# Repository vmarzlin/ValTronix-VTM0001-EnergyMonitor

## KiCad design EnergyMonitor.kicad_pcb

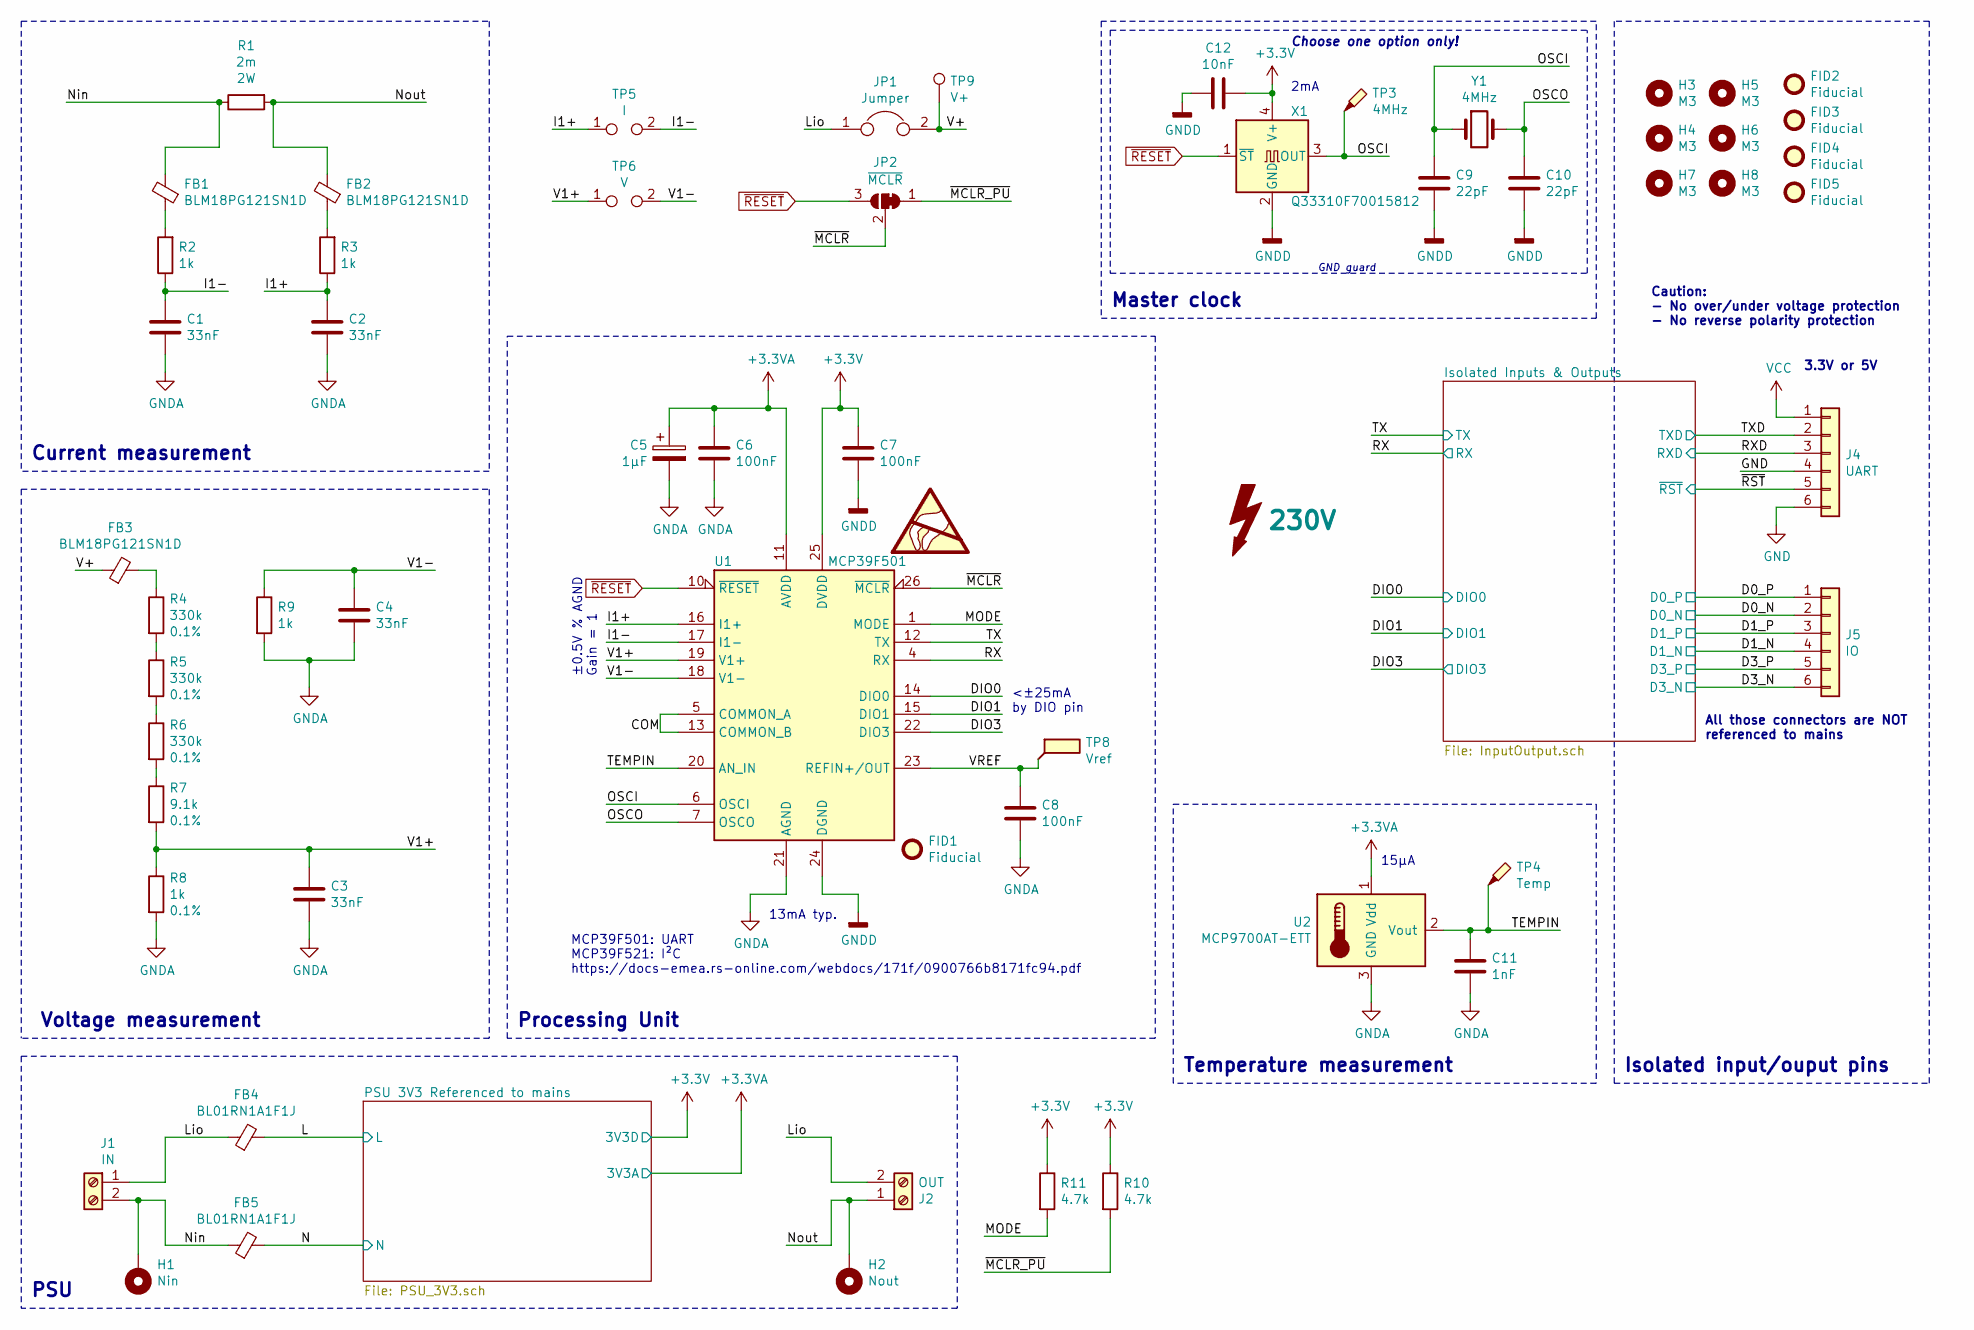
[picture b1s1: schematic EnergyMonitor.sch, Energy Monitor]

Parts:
C1, C2, C3, C4: 33nF; C_0805
C5: 1µF; CP_Elec_4x5.7
C6, C7: 100nF; C_1206
C8: 100nF; C_0805
C9, C10: 22pF; C_0805
C11: 1nF; C_0603
C12: 10nF; C_0603
FB1, FB2, FB3: BLM18PG121SN1D; L_0805
FB4, FB5: BL01RN1A1F1J; L_FB_BL01
FID1: Fiducial; Fiducial_0.5mm_Dia_1mm_Outer
FID2, FID3, FID4, FID5: Fiducial; Fiducial_1mm_Dia_2mm_Outer
H1: Nin; MountingHole_3.2mm_M3_ISO14580_Pad
H2: Nout; MountingHole_3.2mm_M3_ISO14580_Pad
H3, H4, H5, H6, H7, H8: M3; MountingHole_3.2mm_M3_DIN965
J1: IN; TerminalBlock_bornier-2_P5.08mm
J2: OUT; TerminalBlock_bornier-2_P5.08mm
J4: UART; Pin_Header_Straight_1x06_Pitch2.54mm
J5: IO; Pin_Header_Straight_1x06_Pitch2.54mm
JP1: Jumper; Pin_Header_Straight_1x02_Pitch2.54mm
JP2: ~MCLR; JP3_SMD_12closed
R1: 2m; R_2512
R2, R3, R8, R9: 1k; R_0805
R4, R5, R6: 330k; R_MicroMELF_MMU-0102
R7: 9.1k; R_MicroMELF_MMU-0102
R10, R11: 4.7k; R_0805
SYM1: 230V; Symbol_HighVoltage_Silk
SYM2: SYM_ESD_Large; ESD-Logo_8.9x8mm_SilkScreen
TP3: 4MHz; Measurement_Point_Round-SMD-Pad_Small
TP4: Temp; Measurement_Point_Round-SMD-Pad_Small
TP5: I; Test_Point_2Pads
TP6: V; Test_Point_2Pads
TP8: Vref; Measurement_Point_Round-SMD-Pad_Small
TP9: V+; Test_Point_Keystone_5019_Minature
U1: MCP39F501; QFN-28-1EP_5x5mm_Pitch0.5mm
U2: MCP9700AT-ETT; SOT-23
X1: Q33310F70015812; Oscillator_SMD_SeikoEpson_SG8002CE-4pin_3.2x2.5mm
Y1: 4MHz; Crystal_HC49-4H_Vertical

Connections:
+3.3VA: C5.1, C6.1, U1.11 (AVDD), U2.1 (Vdd); also elsewhere on the board
/COM: U1.5 (COMMON_A), U1.13 (COMMON_B)
/D0_N: J5.2; also elsewhere on the board
/D0_P: J5.1; also elsewhere on the board
/D1_N: J5.4; also elsewhere on the board
/D1_P: J5.3; also elsewhere on the board
/D3_N: J5.6; also elsewhere on the board
/D3_P: J5.5; also elsewhere on the board
/DIO0: U1.14 (DIO0); also elsewhere on the board
/DIO1: U1.15 (DIO1); also elsewhere on the board
/DIO3: U1.22 (DIO3); also elsewhere on the board
/I1+: C2.1, R3.1, TP5.1, U1.16 (I1+)
/I1-: C1.1, R2.1, TP5.2, U1.17 (I1-)
/L: FB4.2; also elsewhere on the board
/Lio: FB4.1, J1.1, J2.2, JP1.1
/MODE: R11.2, U1.1 (MODE)
/N: FB5.2; also elsewhere on the board
/Nin: FB1.2, FB5.1, H1.1, J1.2, R1.1
/Nout: FB2.2, H2.1, J2.1, R1.2
/OSCI: C9.1, TP3.1, U1.6 (OSCI), X1.3 (OUT), Y1.1
/OSCO: C10.1, U1.7 (OSCO), Y1.2
/RX: U1.4 (RX); also elsewhere on the board
/RXD: J4.3; also elsewhere on the board
/TEMPIN: C11.1, TP4.1, U1.20 (AN_IN), U2.2 (Vout)
/TX: U1.12 (TX); also elsewhere on the board
/TXD: J4.2; also elsewhere on the board
/V1+: C3.1, R7.2, R8.1, TP6.1, U1.19 (V1+)
/V1-: C4.1, R9.1, TP6.2, U1.18 (V1-)
/V+: FB3.1, JP1.2, TP9.1
/VREF: C8.1, TP8.1, U1.23 (REFIN+/OUT)
/~MCLR: JP2.2 (C), U1.26 (~MCLR)
/~MCLR_PU: JP2.1 (A), R10.2
/~RST: J4.5; also elsewhere on the board
GND: J4.4, J4.6; also elsewhere on the board
GNDA: C1.2, C2.2, C3.2, C4.2, C5.2, C6.2, C8.2, C11.2, R8.2, R9.2, U1.21 (AGND), U2.3 (GND); also elsewhere on the board
GNDD: C7.2, C9.2, C10.2, C12.2, U1.24 (DGND), U1.27 (DGND), U1.29 (DGND), X1.2 (GND); also elsewhere on the board
unnamed: FB1.1, R2.2
unnamed: FB2.1, R3.2
unnamed: FB3.2, R4.1
unnamed: R4.2, R5.1
unnamed: R5.2, R6.1
unnamed: R6.2, R7.1
VCC: J4.1; also elsewhere on the board
~RESET: JP2.3 (B), U1.10 (~RESET), X1.1 (~ST); also elsewhere on the board

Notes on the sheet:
MCP39F501: UART MCP39F521: I²C https://docs-emea.rs-online.com/webdocs/171f/0900766b8171fc94.pdf
13mA typ.
±0.5V % AGND Gain = 1
15µA
2mA
GND guard
3.3V or 5V
<±25mA by DIO pin
Isolated input/ouput pins
Current measurement
Voltage measurement
PSU
Temperature measurement
Processing Unit
Master clock
Caution: - No over/under voltage protection - No reverse polarity protection
All those connectors are NOT referenced to mains
Choose one option only!

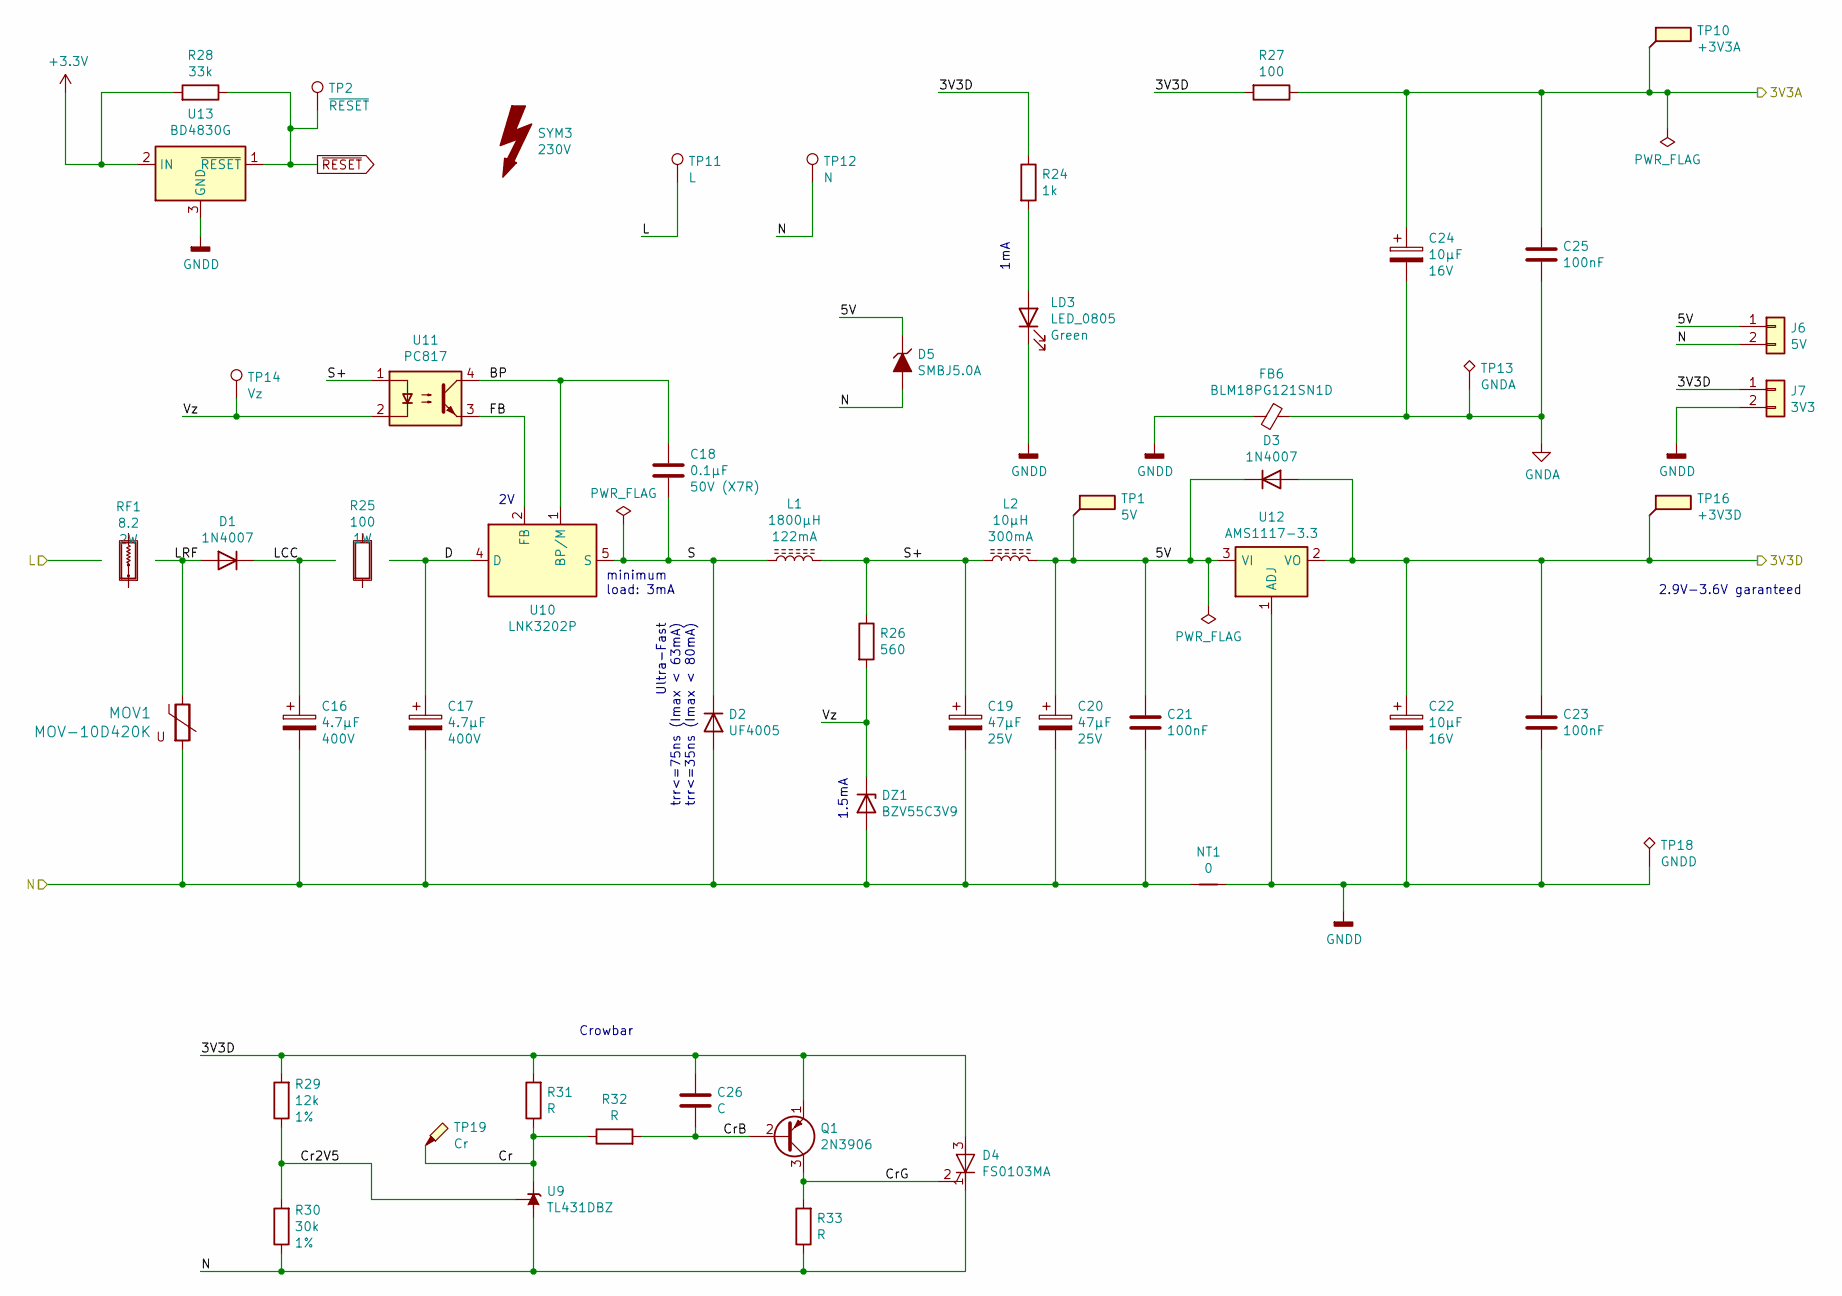
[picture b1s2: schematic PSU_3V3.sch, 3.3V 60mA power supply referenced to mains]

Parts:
C16, C17: 4.7µF; CP_Radial_D10.0mm_P5.00mm; Voltage 400V; Part ULD2G4R7MPD
C18: 0.1µF; C_1206; Voltage 50V (X7R); Part CL31B104KBCNNNL
C19, C20: 47µF; CP_Elec_6.3x7.7; Voltage 25V
C21, C23: 100nF; C_1206
C22, C24: 10µF; CP_Elec_4x5.7; Voltage 16V
C25: 100nF; C_0805
C26: C; C_0805
D1, D3: 1N4007; D_DO-41_SOD81_P10.16mm_Horizontal
D2: UF4005; D_DO-41_SOD81_P10.16mm_Horizontal
D4: FS0103MA; TO-92_Inline_Narrow_Oval
D5: SMBJ5.0A; D_SMB
DZ1: BZV55C3V9; D_MiniMELF
FB6: BLM18PG121SN1D; L_0805
J6: 5V; Pin_Header_Straight_1x02_Pitch2.54mm
J7: 3V3; Pin_Header_Straight_1x02_Pitch2.54mm
L1: 1800µH; L_Bourns_SDR1006; Part SDR1006-182KL
L2: 10µH; L_1210; Part LQH32CN100K23L
LD3: LED_0805
MOV1: MOV-10D420K; RV_Disc_D12_W4.5_P7.5
NT1: 0; R_0805
Q1: 2N3906; TO-92_Inline_Narrow_Oval
R24: 1k; R_0805
R25: 100; R_Axial_DIN0414_L11.9mm_D4.5mm_P15.24mm_Horizontal; Part # ROX2SJ100R
R26: 560; R_0805
R27: 100; R_0805
R28: 33k; R_0805
R29: 12k; R_0805
R30: 30k; R_0805
R31, R32, R33: R; R_0805
RF1: 8.2; R_Axial_DIN0414_L11.9mm_D4.5mm_P15.24mm_Horizontal; Part # PR02000208208JA100
SYM3: 230V; Symbol_HighVoltage_Silk
TP1: 5V; Measurement_Point_Square-SMD-Pad_Big
TP2: ~RESET; Measurement_Point_Round-SMD-Pad_Small
TP10: +3V3A; Measurement_Point_Square-SMD-Pad_Big
TP11: L; Measurement_Point_Square-SMD-Pad_Small
TP12: N; Measurement_Point_Round-TH_Big
TP13: GNDA; Measurement_Point_Round-TH_Big
TP14: Vz; Measurement_Point_Round-SMD-Pad_Small
TP16: +3V3D; Measurement_Point_Square-SMD-Pad_Big
TP18: GNDD; Measurement_Point_Round-TH_Big
TP19: Cr; Measurement_Point_Round-SMD-Pad_Small
U9: TL431DBZ; SOT-23
U10: LNK3202P; PDIP-8C
U11: PC817; DIP-4_W7.62mm_LongPads
U12: AMS1117-3.3; SOT-223-3_TabPin2
U13: BD4830G; SSOP-5_2.9x2.8mm_Pitch0.95mm

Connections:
+3.3VA: C24.1, C25.1, R27.1, TP10.1; also elsewhere on the board
/L: RF1.1, TP11.1; also elsewhere on the board
/N: C16.2, C17.2, C19.2, C20.2, C21.2, D2.2 (A), D4.1 (K), D5.2 (A2), DZ1.2 (A), J6.2, MOV1.2, NT1.2, R30.1, R33.1, TP12.1, U9.3 (A); also elsewhere on the board
/PSU 3V3 Referenced to mains/5V: C20.1, C21.1, D3.1 (K), D5.1 (A1), J6.1, L2.2, TP1.1, U12.3 (VI)
/PSU 3V3 Referenced to mains/BP: C18.1, U10.1 (BP/M), U11.4
/PSU 3V3 Referenced to mains/Cr: R31.1, R32.1, TP19.1, U9.1 (K)
/PSU 3V3 Referenced to mains/Cr2V5: R29.1, R30.2, U9.2 (REF)
/PSU 3V3 Referenced to mains/CrB: C26.2, Q1.2 (B), R32.2
/PSU 3V3 Referenced to mains/CrG: D4.2 (G), Q1.3 (C), R33.2
/PSU 3V3 Referenced to mains/D: C17.1, R25.2, U10.4 (D)
/PSU 3V3 Referenced to mains/FB: U10.2 (FB), U11.3
/PSU 3V3 Referenced to mains/LCC: C16.1, D1.1 (K), R25.1
/PSU 3V3 Referenced to mains/LRF: D1.2 (A), MOV1.1, RF1.2
/PSU 3V3 Referenced to mains/S: C18.2, D2.1 (K), L1.1, U10.5 (S), U10.6 (S), U10.7 (S), U10.8 (S)
/PSU 3V3 Referenced to mains/S+: C19.1, L1.2, L2.1, R26.1, U11.1
/PSU 3V3 Referenced to mains/Vz: DZ1.1 (K), R26.2, TP14.1, U11.2
GNDA: C24.2, C25.2, FB6.1, TP13.1; also elsewhere on the board
GNDD: C22.2, C23.2, FB6.2, J7.2, LD3.1 (K), NT1.1, TP18.1, U12.1 (ADJ), U13.3 (GND); also elsewhere on the board
unnamed: LD3.2 (A), R24.2
~RESET: R28.1, TP2.1, U13.1 (~RESET); also elsewhere on the board

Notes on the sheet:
Ultra-Fast trr<=75ns (Imax < 63mA) trr<=35ns (Imax < 80mA)
1.5mA
minimum load: 3mA
Crowbar
1mA
2.9V-3.6V garanteed

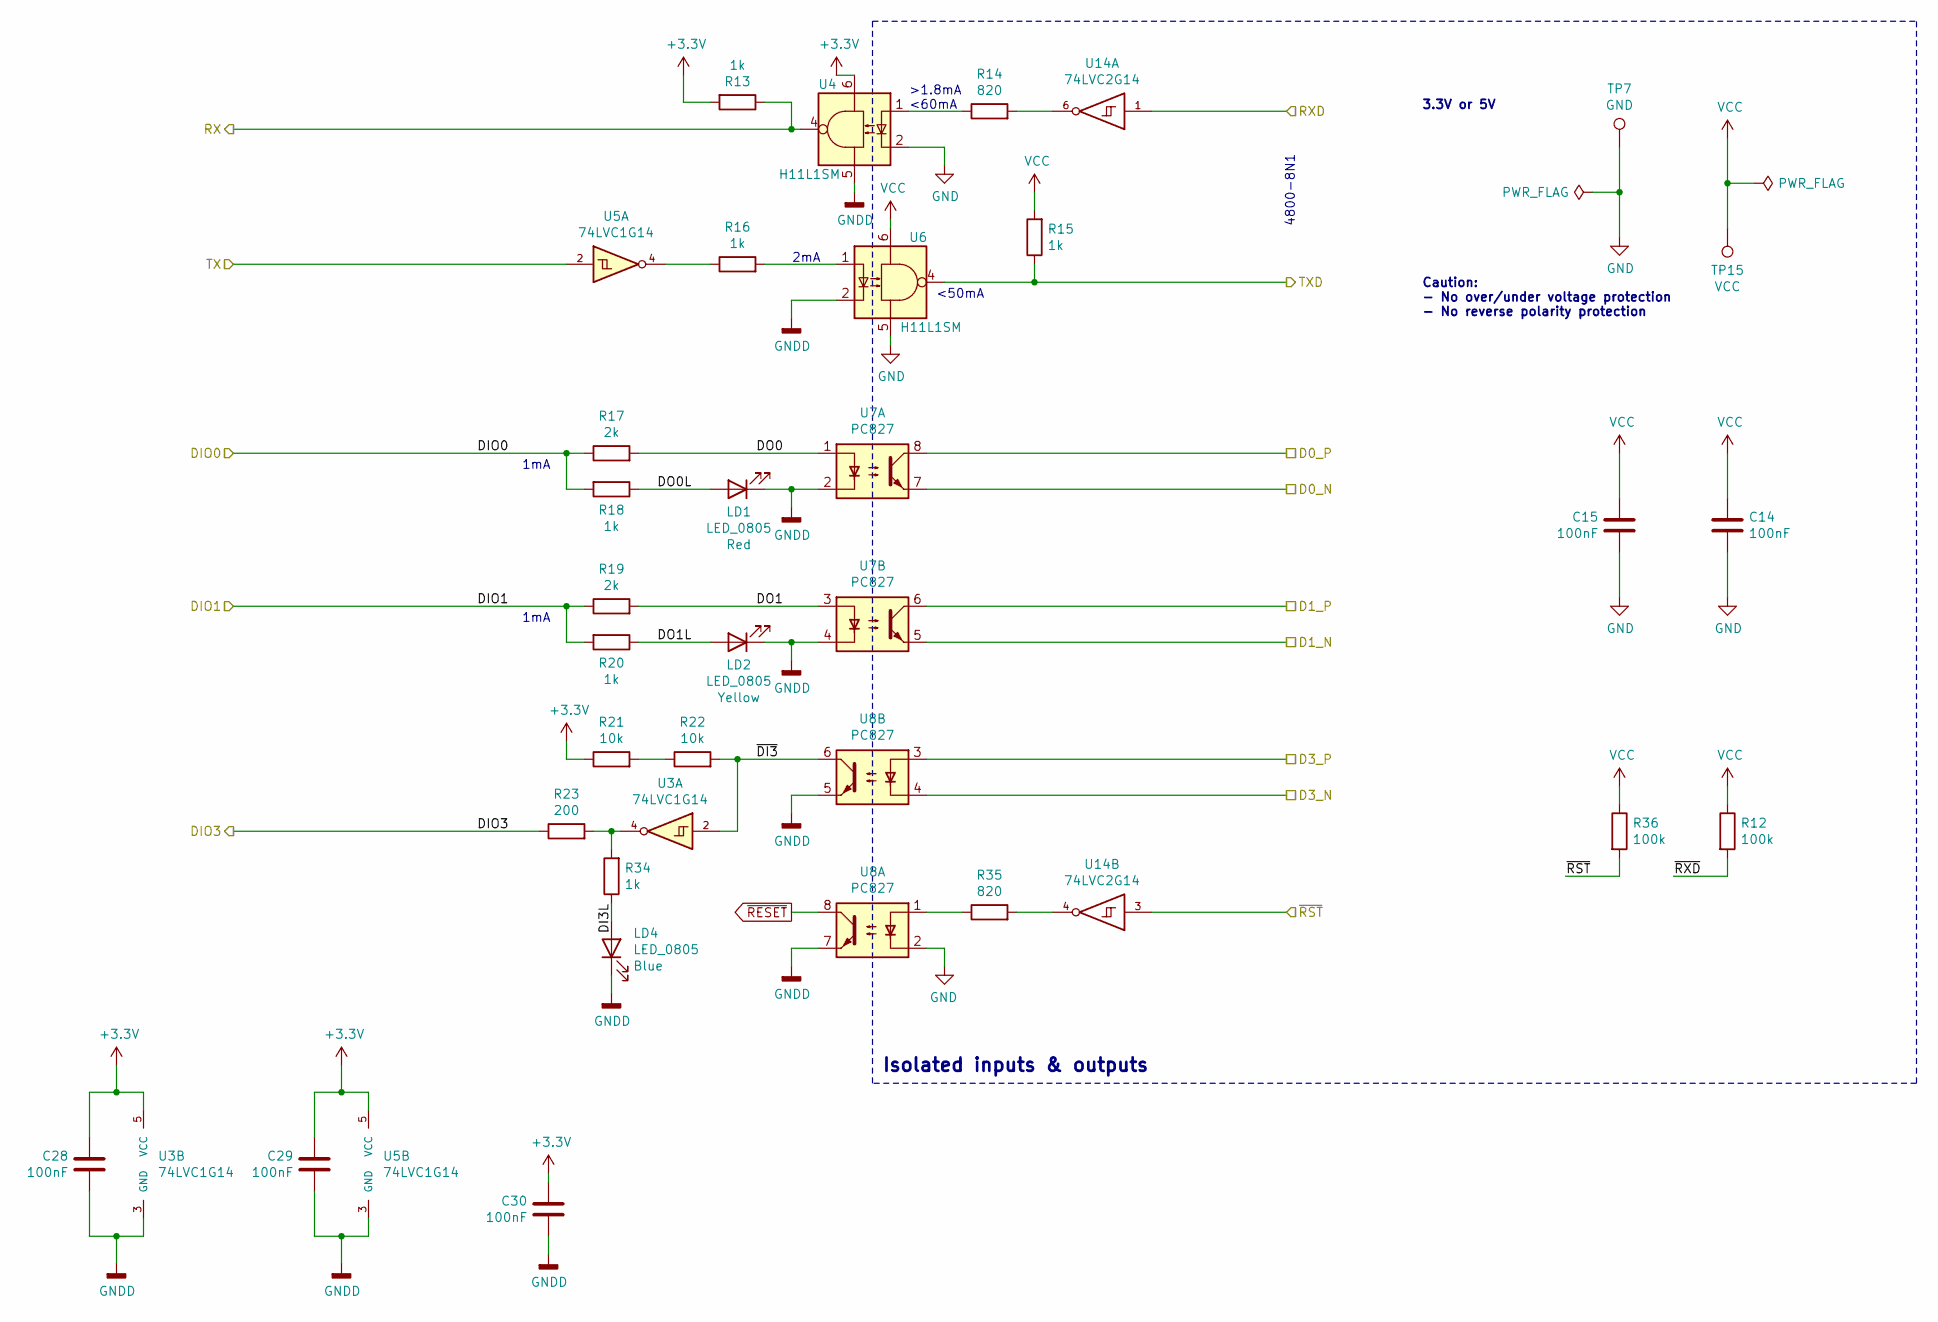
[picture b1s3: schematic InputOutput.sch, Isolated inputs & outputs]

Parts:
C14, C30: 100nF; C_0805; Part 08055C104KAT2A
C15: 100nF; C_0603; Part 08055C104KAT2A
C28, C29: 100nF; C_0603
LD1, LD2, LD4: LED_0805
R12, R36: 100k; R_0805
R13, R15, R16, R18, R20, R34: 1k; R_0805
R14, R35: 820; R_0805
R17, R19: 2k; R_0805
R21, R22: 10k; R_0805
R23: 200; R_0805
TP7: GND; Measurement_Point_Round-TH_Big
TP15: VCC; Measurement_Point_Square-SMD-Pad_Big
U3, U5: 74LVC1G14; SOT-25
U4, U6: H11L1SM; SMDIP-6_W9.53mm
U7, U8: PC827; SMDIP-8_W9.53mm
U14: 74LVC2G14; SOT-363_SC-70-6

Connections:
/D0_N: U7.7; also elsewhere on the board
/D0_P: U7.8; also elsewhere on the board
/D1_N: U7.5; also elsewhere on the board
/D1_P: U7.6; also elsewhere on the board
/D3_N: U8.4; also elsewhere on the board
/D3_P: U8.3; also elsewhere on the board
/DIO0: R17.1, R18.2; also elsewhere on the board
/DIO1: R19.1, R20.2; also elsewhere on the board
/DIO3: R23.1; also elsewhere on the board
/Isolated Inputs & Outputs/DI3L: LD4.2 (A), R34.1
/Isolated Inputs & Outputs/DO0: R17.2, U7.1
/Isolated Inputs & Outputs/DO0L: LD1.2 (A), R18.1
/Isolated Inputs & Outputs/DO1: R19.2, U7.3
/Isolated Inputs & Outputs/DO1L: LD2.2 (A), R20.1
/Isolated Inputs & Outputs/~DI3: R22.2, U3.2, U8.6
/Isolated Inputs & Outputs/~RXD: R12.2
/RX: R13.1, U4.4; also elsewhere on the board
/RXD: U14.1; also elsewhere on the board
/TX: U5.2; also elsewhere on the board
/TXD: R15.1, U6.4; also elsewhere on the board
/~RST: R36.2, U14.3; also elsewhere on the board
GND: C14.1, C15.1, TP7.1, U4.2, U6.5, U8.2, U14.2 (GND); also elsewhere on the board
GNDD: C28.2, C29.2, C30.2, LD1.1 (K), LD2.1 (K), LD4.1 (K), U3.3 (GND), U4.5, U5.3 (GND), U6.2, U7.2, U7.4, U8.5, U8.7; also elsewhere on the board
unnamed: R14.1, U4.1
unnamed: R14.2, U14.6
unnamed: R16.1, U5.4
unnamed: R16.2, U6.1
unnamed: R21.2, R22.1
unnamed: R23.2, R34.2, U3.4
unnamed: R35.1, U8.1
unnamed: R35.2, U14.4
VCC: C14.2, C15.2, R12.1, R15.2, R36.1, TP15.1, U6.6, U14.5 (VCC); also elsewhere on the board
~RESET: U8.8; also elsewhere on the board

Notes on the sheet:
2mA
1mA
4800-8N1
>1.8mA <60mA
<50mA
Isolated inputs & outputs
Caution: - No over/under voltage protection - No reverse polarity protection
3.3V or 5V

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
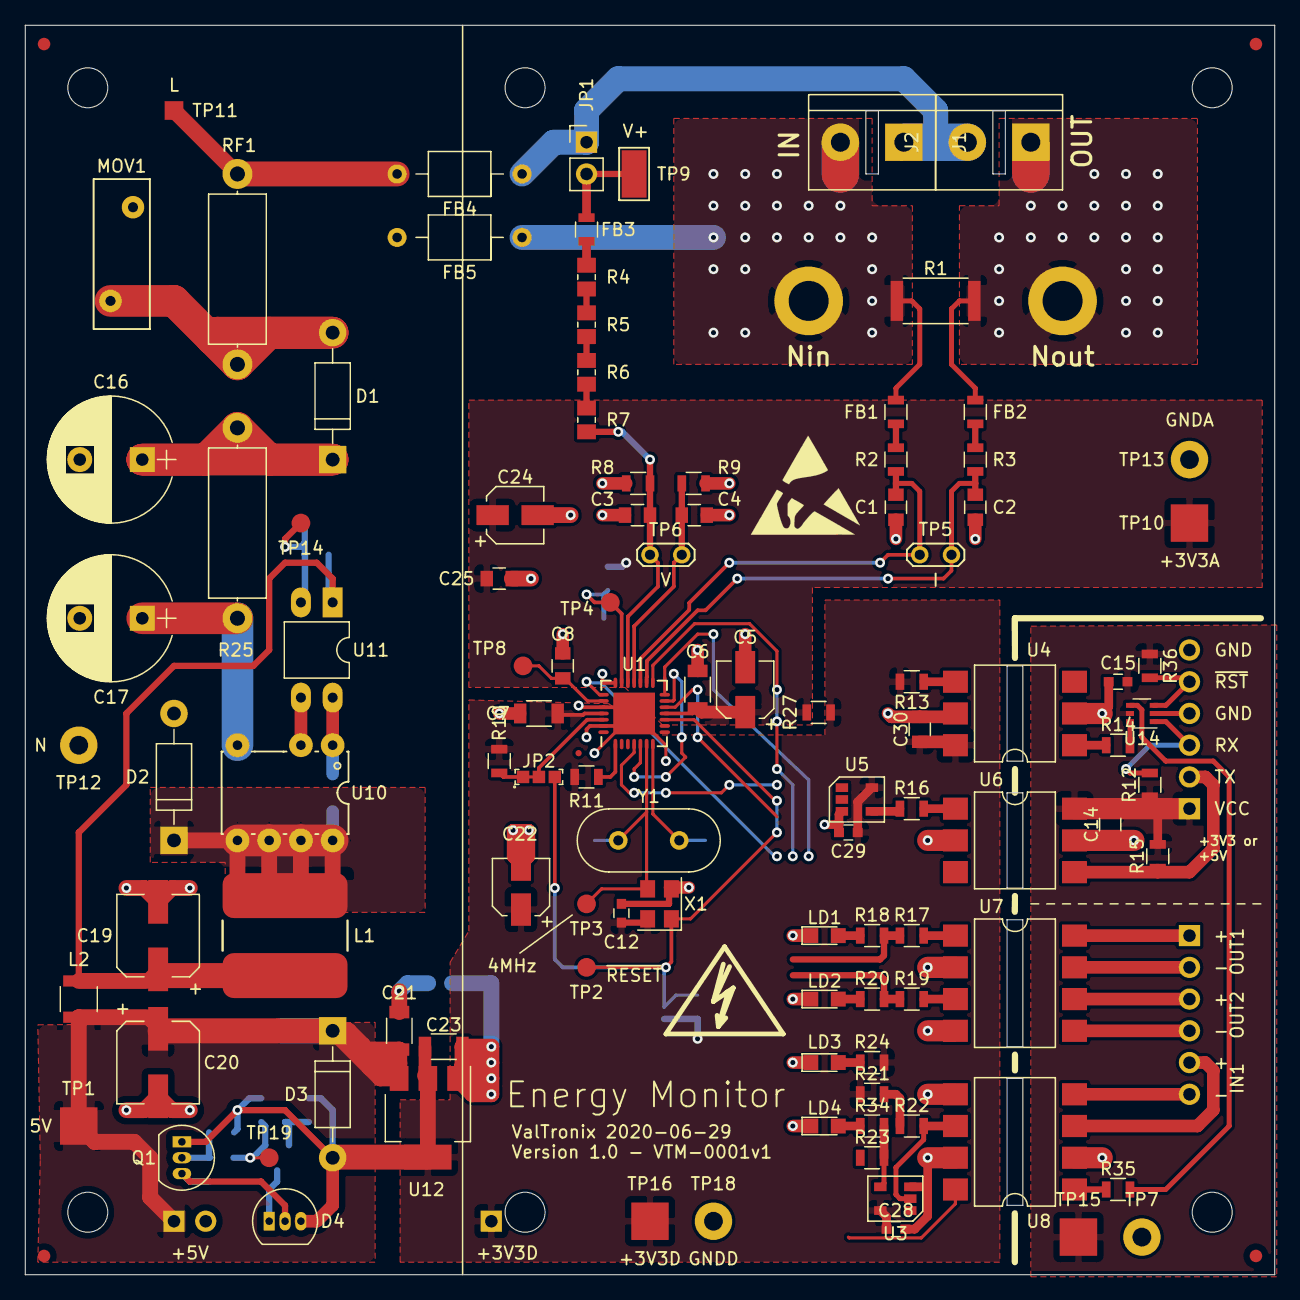
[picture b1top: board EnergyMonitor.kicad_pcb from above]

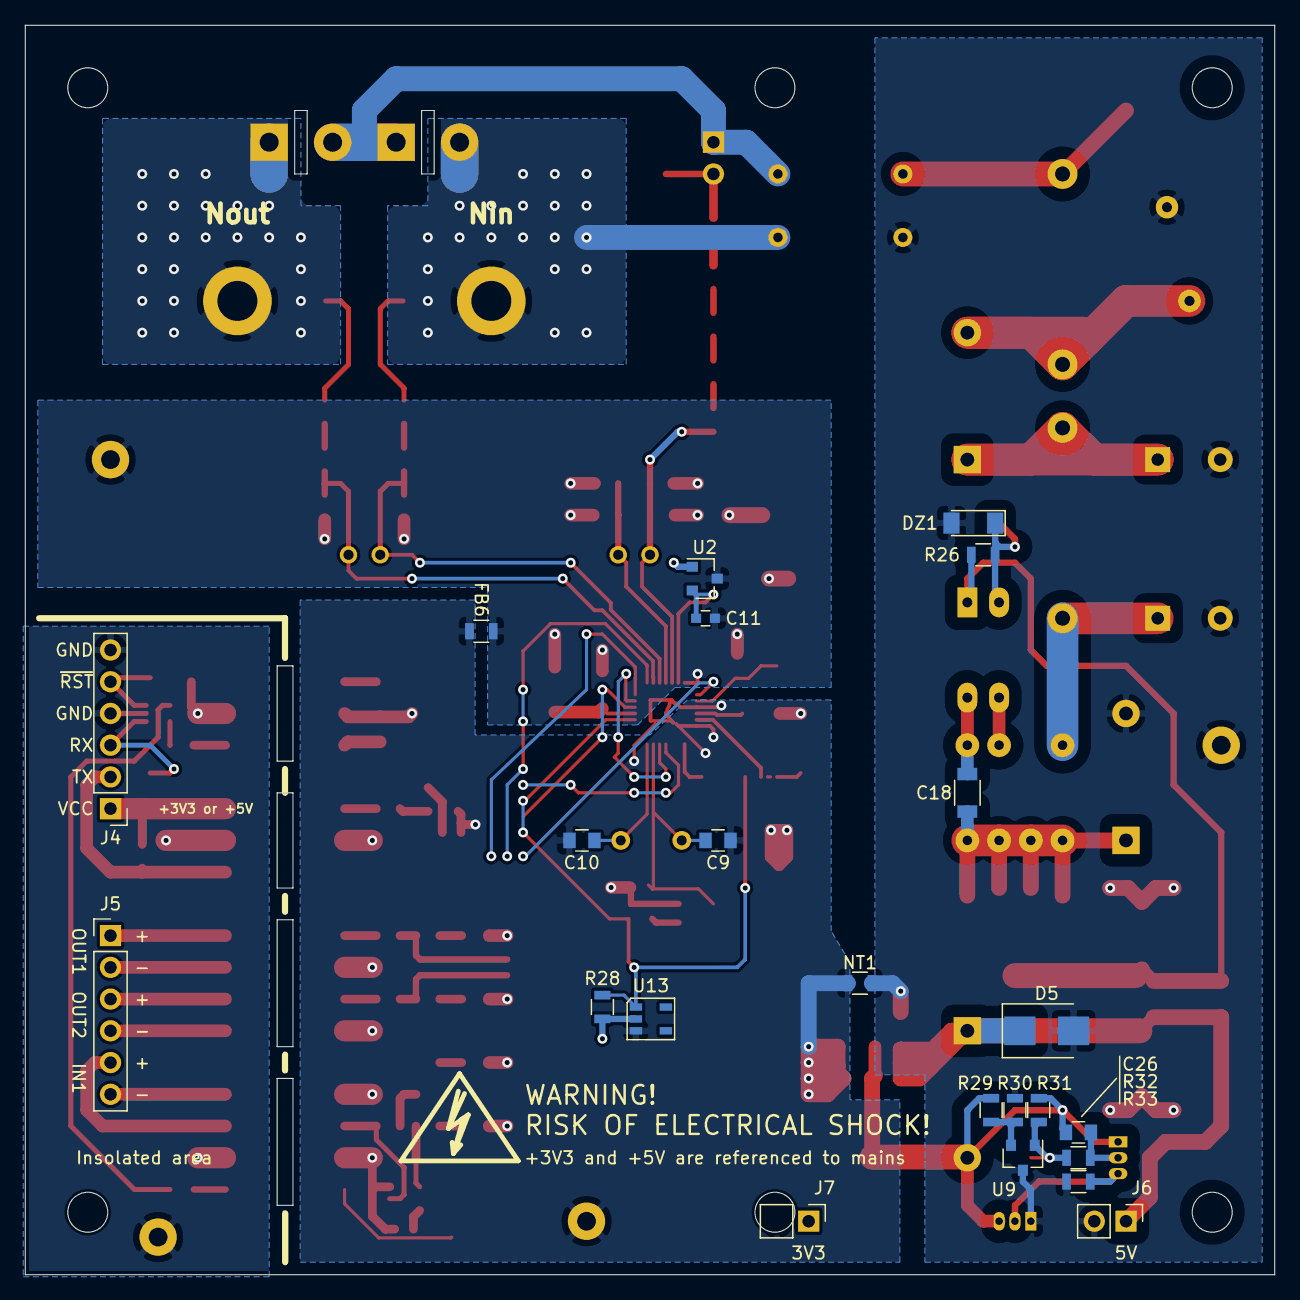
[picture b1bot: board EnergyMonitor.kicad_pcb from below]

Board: 2 copper layers, 100.0 x 100.0 mm, 144 parts (24 on the bottom side), 73 nets.

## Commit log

2020-06-01 Initial commit
    DRC/ERC ok
2020-06-24 Minor fixes
    Some typos
    Fix test point outline
    DRC/ERC pass
2020-07-01 Routage
2020-07-01 Préparation pour production
2020-07-04 Applying Templace
    Change directories to follow ValTronix-VTM0000 Template
2020-07-04 Removing unused Libraries
2020-07-05 Adding simulations
2021-01-14 Ajout de la BOM
2021-01-15 Create stale.yml
    Adding a job to mark stale issues and pull requests
2022-09-08 Première version produite
